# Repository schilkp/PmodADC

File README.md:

# PmodADC

### Philipp Schilk, 2020

## Description
A fully discrete 14bit, 41kHz, Successive-Approximation Audio ADC and 14bit 41kHz R2R Audio DAC 
controlled by an [iCEBreaker FPGA board](https://1bitsquared.com/collections/fpga/products/icebreaker). 

## Details

## Demos

These are a few demonstrations of the PmodADC and PmodDAC.

For each song, there are 3 files provided:  
    - The original (mono) wav file  
    - The song played back via a phone and recorded on the PmodADC  
    - The song played via the PmodDAC and recorded with a Focusrite Saffire Pro 40 Interface.  

Note that all audio files are provided at 44.1kHz to allow for easier playback:  
The PmodADC demos were played back at 44.1kHz and upsampled from 41kHz after recording.  
The PmodDAC demos were downsampled to 41kHz for playback, and recorded at 44.1kHz.   

All music by Kevin MacLeod, see Music Attribution below.

The wav files can be found [here](Doc/Demos), or via the Soundcloud links below:

| *Song* 	| *Original* 	| *PmodADC Demo* 	| *PmodDAC Demo* 	|
|:-:	|:-:	|:-:	|:-:	|
| New Hero in Town 	| [here](https://soundcloud.com/user-489490213/new-hero-in-town-reference/s-YKGpP2wkpSc) 	| [here](https://soundcloud.com/user-489490213/new-hero-in-town-pmodadc/s-A1OPIKn5Tv4) 	| [here](https://soundcloud.com/user-489490213/new-hero-in-town-pmoddac/s-smGRP41zKKE) 	|
| Protofunk 	| [here](https://soundcloud.com/user-489490213/protofunk-reference/s-mYtDzv4H0rD) 	| [here](https://soundcloud.com/user-489490213/protofunk-pmodadc/s-5CrWlwWIQJU) 	| [here](https://soundcloud.com/user-489490213/protofunk-pmoddac/s-AqIKrZKs7Aa) 	|
| Whiskey on the Mississippi 	| [here](https://soundcloud.com/user-489490213/whiskey-on-the-mississippi-reference/s-0ekaJDO2ERm) 	| [here](https://soundcloud.com/user-489490213/whiskey-on-the-mississippi-pmodadc/s-d2xfiT4uBGa) 	| [here](https://soundcloud.com/user-489490213/whiskey-on-the-mississippi-pmoddac/s-CflAaRhN0gA) 	|
| The Parting 	| [here](https://soundcloud.com/user-489490213/the-parting-reference/s-s09MCjP3SIX) 	| [here](https://soundcloud.com/user-489490213/the-parting-pmodadc/s-gcHSaS2ZzWT) 	| [here](https://soundcloud.com/user-489490213/the-parting-pmoddac/s-kLg3MuZsgWg) 	|

Alternatively, a single website with all the above audio files can be found [here](https://soundcloud.com/user-489490213/sets/pmodadc-demonstration/s-fJryQAe7XSp).

## Setup

A guide to setting up the open-source [apio](https://github.com/FPGAwars/apio) tool-chain can be found [here](Doc/ToolchainSetup.md).   

This project requires some hardware modifications to the iCEbreaker board. See [here](Doc/iCEBreakerMod.md) for details.  

The Python/Matlab scripts to play and record audio require some drivers and setup. See [here](Doc/FT2232H_Setup.md) for details.  

Two versions of the Verilog Code are provided:  
	- Setup 1, which immediately plays back the audio recorded by the PmodADC via the PmodDAC.  
	- Setup 2, which allows the PmodADC and PmodDAC to send/receive audio via USB.
	
See [here](iCEbreaker_HDL/Setup%20Description.md) for details.

## Python Utilities

The easiest way to record and play music is using the two python utilities provided [here](Scripts/Python/).

They rely on numpy, pyserial, wavio, and scipy:

```bash
> pip install -r requirements.txt
```

They have only been tested under python3.

### Record.py

Record music to a wav file using the PmodADC.

By default the audio is resampled to 44.1kHz.

Usage:

```
usage: Record.py [-h] (-s S | -n N | -i) [-r] comport outfile

positional arguments:
  comport     The COM port to which the board is connected.
  outfile     The filename under which the recorded audio should be saved.

optional arguments:
  -h, --help  show this help message and exit
  -s S        The number of seconds that should be recorded.
  -n N        The number of samples that should be recorded.
  -i          Recorded until a Keyboard Interrupt is received.
  -r          Do not re-sample audio to 44.1khz.
```

Record 10 seconds of audio from COM8 and save it to recording.wav:

```bash
python3 Record.py COM8 recording.wav -s 10
```

### Play.py

Play a wav file via the PmodDAC.

By default the wav file is resampled to 41kHz (if necessary). 

Usage:
```
usage: Play.py [-h] [-L | -R] [-r] comport wavfile

positional arguments:
  comport     The COM port to which the board is connected.
  wavfile     The filename of the audio file.

optional arguments:
  -h, --help  show this help message and exit
  -L          Play the left audio channel.
  -R          Play the right audio channel.
  -r          Do not re-sample audio to 41kHz.
```

Play the left channel of some_audio_file.wav via COM8:

```bash
python3 Play.py COM8 some_audio_file.wav -L
```

## Matlab Utilities

Matlab functions to communicate with the PmodADC/PmodDAC are also provided. 

See [Scripts/MATLAB/RecordAudioExample.m](Scripts/MATLAB/RecordAudioExample.m) and [Scripts/MATALB/PlayAudioExample.m](Scripts/MATALB/PlayAudioExample.m)

## Music Attribution

```
Protofunk by Kevin MacLeod  
Link: https://incompetech.filmmusic.io/song/4247-protofunk  
License: http://creativecommons.org/licenses/by/4.0/  

Whiskey on the Mississippi by Kevin MacLeod  
Link: https://incompetech.filmmusic.io/song/4624-whiskey-on-the-mississippi  
License: http://creativecommons.org/licenses/by/4.0/  
  
New Hero In Town by Kevin MacLeod  
Link: https://incompetech.filmmusic.io/song/5742-new-hero-in-town  
License: http://creativecommons.org/licenses/by/4.0/  

The Parting by Kevin MacLeod  
Link: https://incompetech.filmmusic.io/song/4501-the-parting  
License: http://creativecommons.org/licenses/by/4.0/  
```

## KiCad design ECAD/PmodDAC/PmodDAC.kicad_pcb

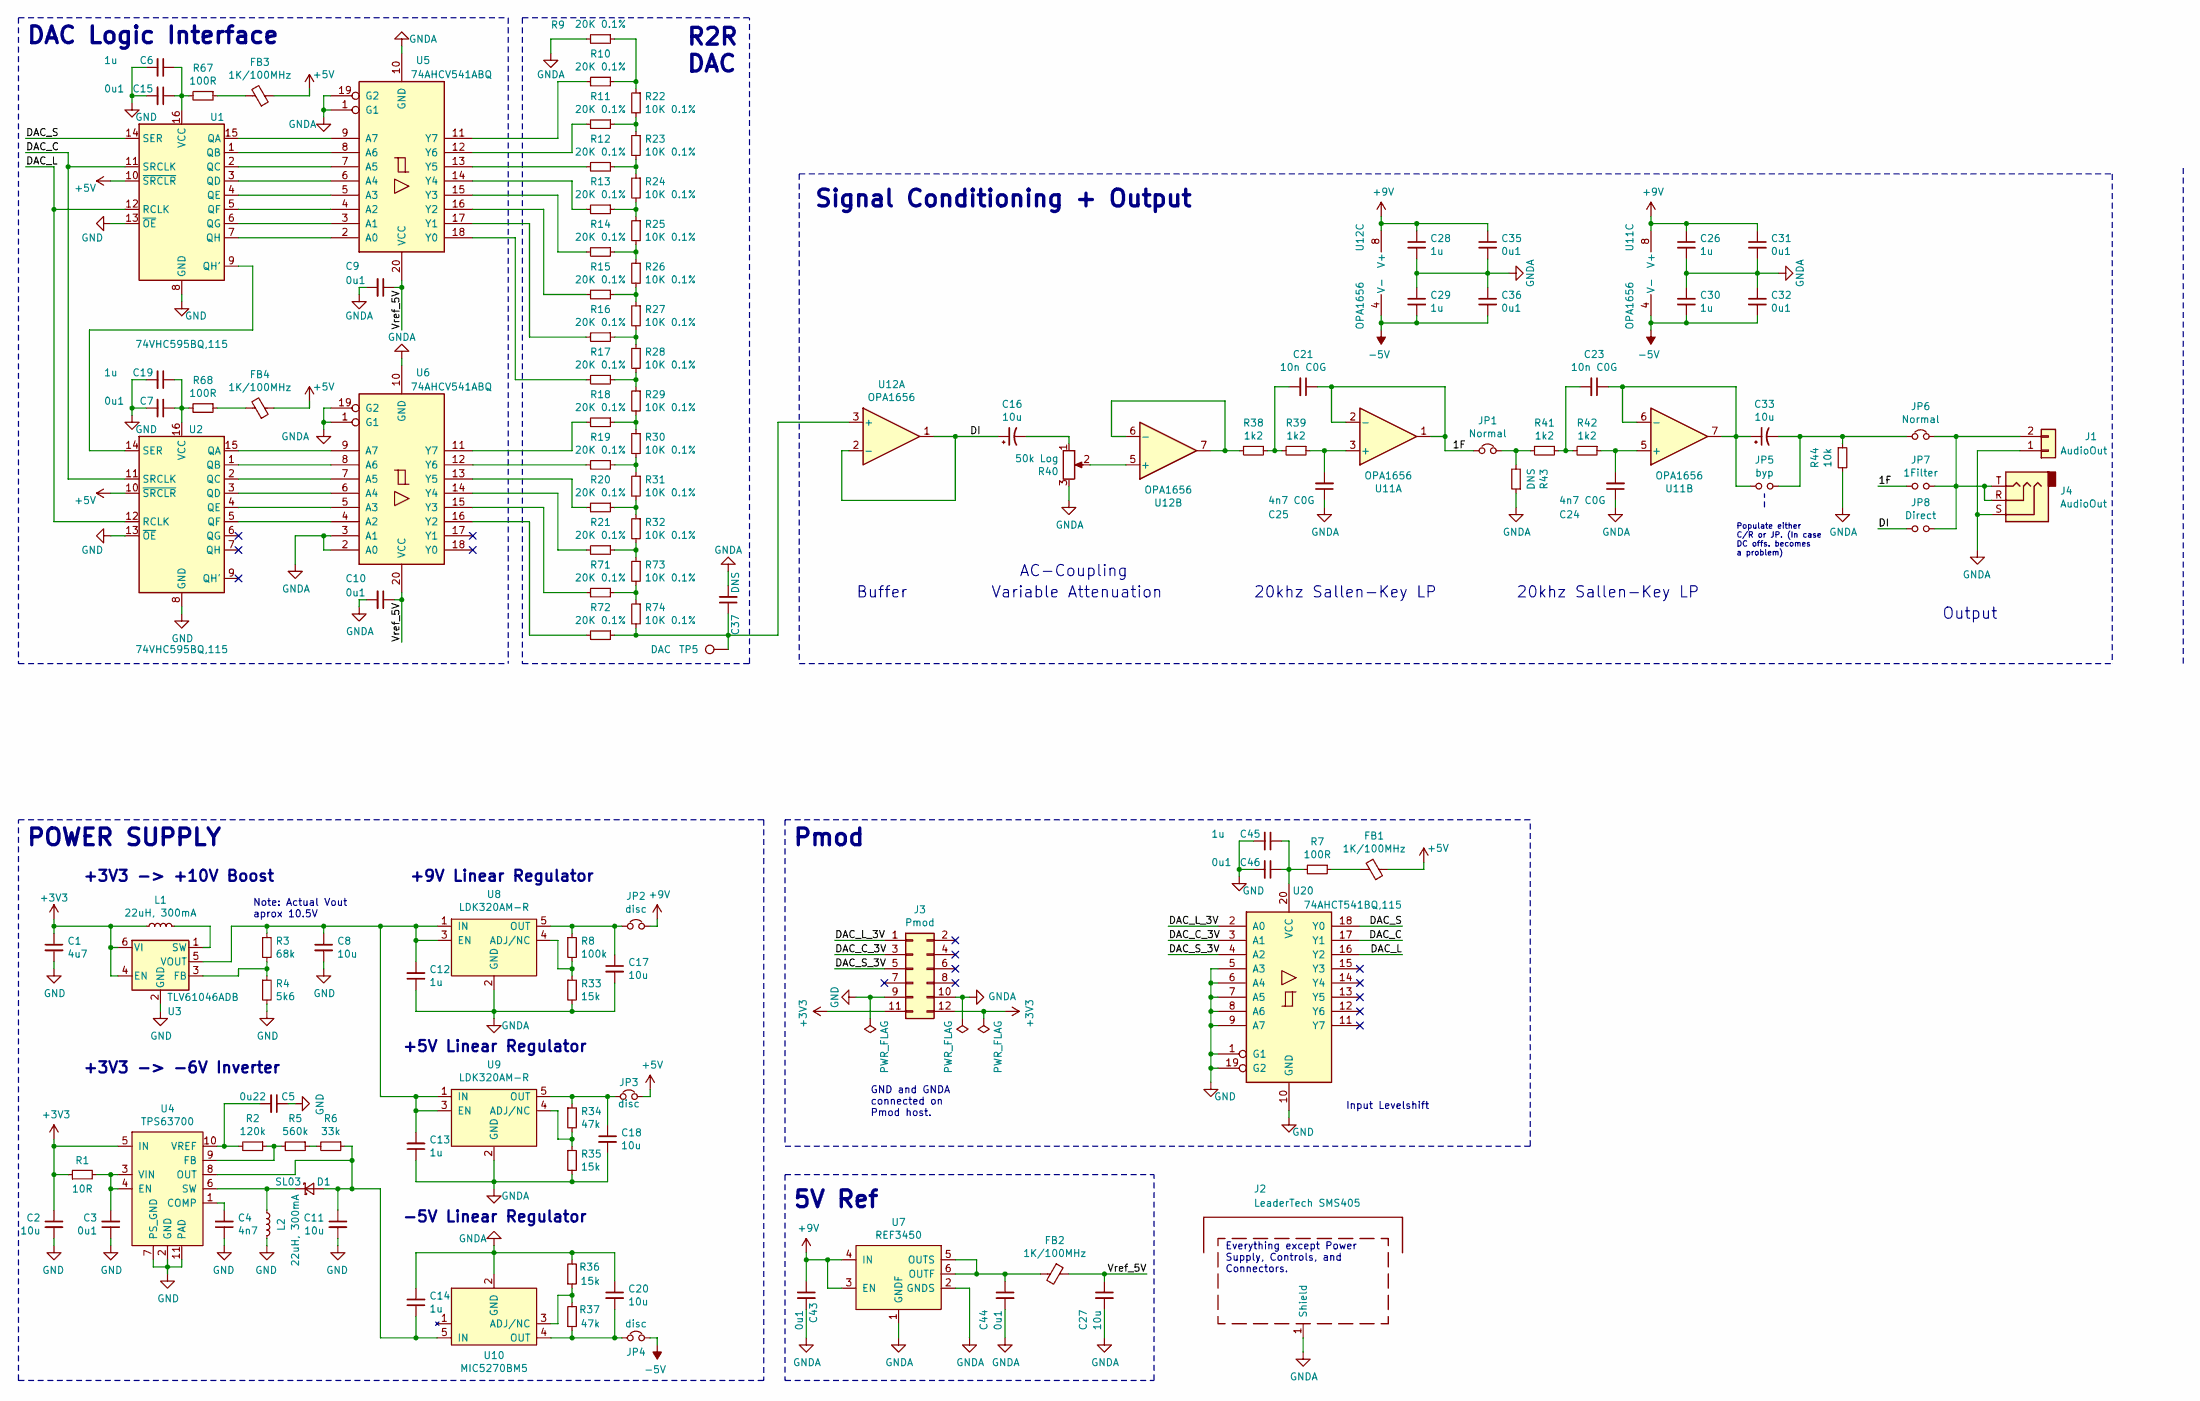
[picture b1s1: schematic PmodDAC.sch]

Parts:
C1: 4u7; C_0805_2012Metric
C2, C8, C11, C17, C18, C20, C27: 10u; C_1206_3216Metric
C3, C7, C9, C10, C15, C31, C32, C35, C36, C43, C44, C46: 0u1; C_0402_1005Metric
C4: 4n7; C_0402_1005Metric
C5: 0u22; C_0402_1005Metric
C6, C12, C13, C14, C19, C26, C28, C29, C30, C45: 1u; C_0402_1005Metric
C16, C33: 10u; CP_Radial_D4.0mm_P1.50mm
C21, C23: 10n C0G; C_0603_1608Metric
C24, C25: 4n7 C0G; C_0603_1608Metric
C37: DNS; C_0402_1005Metric
D1: SL03; D_SMF
FB1, FB2, FB3, FB4: 1K/100MHz; L_0402_1005Metric
J1: AudioOut; PinHeader_1x02_P2.54mm_Vertical
J2: LeaderTech SMS405; Leader_SMS405
J3: Pmod; PinHeader_2x06_P2.54mm_Vertical
J4: AudioOut; PJ-313D-6A
JP1, JP6: Normal; R_0402_1005Metric
JP2, JP3, JP4: disc; R_0402_1005Metric
JP5: byp; R_0402_1005Metric
JP7: 1Filter; R_0402_1005Metric
JP8: Direct; R_0402_1005Metric
L1, L2: 22uH, 300mA; L_Wuerth_MAPI-3020
R1: 10R; R_0402_1005Metric
R2: 120k; R_0402_1005Metric
R3: 68k; R_0402_1005Metric
R4: 5k6; R_0402_1005Metric
R5: 560k; R_0402_1005Metric
R6: 33k; R_0402_1005Metric
R7, R67, R68: 100R; R_0402_1005Metric
R8: 100k; R_0402_1005Metric
R9, R10, R11, R12, R13, R14, R15, R16, R17, R18, R19, R20, R21, R71, R72: 20K 0.1%; R_0402_1005Metric
R22, R23, R24, R25, R26, R27, R28, R29, R30, R31, R32, R73, R74: 10K 0.1%; R_0402_1005Metric
R33, R35, R36: 15k; R_0402_1005Metric
R34, R37: 47k; R_0402_1005Metric
R38, R39, R41, R42: 1k2; R_0402_1005Metric
R40: 50k Log; Potentiometer_Alps_RK09L_Single_Vertical
R43: DNS; R_0402_1005Metric
R44: 10k; R_0402_1005Metric
TP5: DAC; TestPoint_Pad_D1.0mm
U1, U2: 74VHC595BQ,115; SOT763-1_DHVQFN16
U3: TLV61046ADB; SOT-23-6
U4: TPS63700; VSON-10-1EP_3x3mm_P0.5mm_EP1.65x2.4mm_ThermalVias
U5, U6: 74AHCV541ABQ; SOT764-1_DHVQFN20
U7: REF3450; SOT-23-6
U8, U9: LDK320AM-R; SOT-23-5
U10: MIC5270BM5; SOT-23-5
U11, U12: OPA1656; SOIC-8_3.9x4.9mm_P1.27mm
U20: 74AHCT541BQ,115; SOT764-1_DHVQFN20

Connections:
+3V3: C1.1, C2.1, J3.11, J3.12, L1.1, R1.1, U3.4 (EN), U3.6 (VI), U4.5 (IN)
+5V: FB1.1, FB3.1, FB4.1, JP3.2, U1.10 (~SRCLR), U2.10 (~SRCLR)
+9V: C26.1, C28.1, C31.1, C35.1, C43.1, JP2.2, U7.3 (EN), U7.4 (IN), U11.8 (V+), U12.8 (V+)
-5V: C29.2, C30.2, C32.2, C36.2, JP4.2, U11.4 (V-), U12.4 (V-)
/1F: C21.1, JP1.1, JP7.1, U11.1, U11.2 (-)
/DAC_C: U1.11 (SRCLK), U2.11 (SRCLK), U20.17 (Y1)
/DAC_C_3V: J3.3, U20.3 (A1)
/DAC_L: U1.12 (RCLK), U2.12 (RCLK), U20.16 (Y2)
/DAC_L_3V: J3.1, U20.2 (A0)
/DAC_S: U1.14 (SER), U20.18 (Y0)
/DAC_S_3V: J3.5, U20.4 (A2)
/DI: C16.1, JP8.1, U12.1, U12.2 (-)
/Vref_5V: C9.1, C10.1, C27.1, FB2.1, U5.20 (VCC), U6.20 (VCC)
GND: C1.2, C2.2, C3.1, C4.1, C5.1, C6.2, C7.2, C8.2, C11.2, C15.2, C19.2, C45.2, C46.2, J3.9, L2.2, R4.2, U1.8 (GND), U1.13 (~OE), U2.8 (GND), U2.13 (~OE), U3.2 (GND), U4.2 (GND), U4.7 (PS_GND), U4.11 (PAD), U20.1 (G1), U20.5 (A3), U20.6 (A4), U20.7 (A5), U20.8 (A6), U20.9 (A7), U20.10 (GND), U20.19 (G2)
GNDA: C9.2, C10.2, C12.1, C13.1, C14.2, C17.2, C18.2, C20.1, C24.1, C25.1, C26.2, C27.2, C28.2, C29.1, C30.1, C31.2, C32.1, C35.2, C36.1, C37.2, C43.2, C44.2, J1.1, J2.1, J3.10, J4.S, R9.2, R33.2, R35.2, R36.2, R40.3, R43.1, R44.2, U5.1 (G1), U5.10 (GND), U5.19 (G2), U6.1 (G1), U6.2 (A0), U6.3 (A1), U6.10 (GND), U6.19 (G2), U7.1 (GNDF), U7.2 (GNDS), U8.2 (GND), U9.2 (GND), U10.2 (GND)
unnamed: C3.2, R1.2, U4.3 (VIN), U4.4 (EN)
unnamed: C4.2, U4.1 (COMP)
unnamed: C5.2, R2.2, U4.10 (VREF)
unnamed: C11.1, C14.1, D1.2 (A), R6.1, U4.8 (OUT), U10.5 (IN)
unnamed: C8.1, C12.2, C13.2, R3.1, U3.5 (VOUT), U8.1 (IN), U8.3 (EN), U9.1 (IN), U9.3 (EN)
unnamed: C6.1, C15.1, R67.2, U1.16 (VCC)
unnamed: C16.2, R40.1
unnamed: C17.1, JP2.1, R8.1, U8.5 (OUT)
unnamed: C18.1, JP3.1, R34.1, U9.5 (OUT)
unnamed: C7.1, C19.1, R68.2, U2.16 (VCC)
unnamed: C20.2, JP4.1, R37.1, U10.4 (OUT)
unnamed: C21.2, R38.1, R39.2
unnamed: C23.1, C33.1, JP5.1, U11.6 (-), U11.7
unnamed: C23.2, R41.1, R42.2
unnamed: C24.2, R42.1, U11.5 (+)
unnamed: C25.2, R39.1, U11.3 (+)
unnamed: C33.2, JP5.2, JP6.1, R44.1
unnamed: C37.1, R72.1, R74.2, TP5.1, U12.3 (+)
unnamed: C44.1, FB2.2, U7.5 (OUTS), U7.6 (OUTF)
unnamed: C45.1, C46.1, R7.2, U20.20 (VCC)
unnamed: D1.1 (K), L2.1, U4.6 (SW)
unnamed: FB1.2, R7.1
unnamed: FB3.2, R67.1
unnamed: FB4.2, R68.1
unnamed: J1.2, J4.R, J4.T, JP6.2, JP7.2, JP8.2
unnamed: JP1.2, R41.2, R43.2
unnamed: L1.2, U3.1 (SW)
unnamed: R2.1, R5.2, U4.9 (FB)
unnamed: R3.2, R4.1, U3.3 (FB)
unnamed: R5.1, R6.2
unnamed: R9.1, R10.1, R22.1
unnamed: R10.2, U5.11 (Y7)
unnamed: R11.1, R22.2, R23.1
unnamed: R11.2, U5.12 (Y6)
unnamed: R12.1, R23.2, R24.1
unnamed: R12.2, U5.13 (Y5)
unnamed: R13.1, R24.2, R25.1
unnamed: R13.2, U5.14 (Y4)
unnamed: R14.1, R25.2, R26.1
unnamed: R14.2, U5.15 (Y3)
unnamed: R15.1, R26.2, R27.1
unnamed: R15.2, U5.16 (Y2)
unnamed: R16.1, R27.2, R28.1
unnamed: R16.2, U5.17 (Y1)
unnamed: R17.1, R28.2, R29.1
unnamed: R17.2, U5.18 (Y0)
unnamed: R18.1, R29.2, R30.1
unnamed: R18.2, U6.11 (Y7)
unnamed: R19.1, R30.2, R31.1
unnamed: R19.2, U6.12 (Y6)
unnamed: R20.1, R31.2, R32.1
unnamed: R20.2, U6.13 (Y5)
unnamed: R21.1, R32.2, R73.1
unnamed: R21.2, U6.14 (Y4)
unnamed: R8.2, R33.1, U8.4 (ADJ/NC)
unnamed: R34.2, R35.1, U9.4 (ADJ/NC)
unnamed: R36.1, R37.2, U10.3 (ADJ/NC)
unnamed: R38.2, U12.6 (-), U12.7
unnamed: R40.2, U12.5 (+)
unnamed: R71.1, R73.2, R74.1
unnamed: R71.2, U6.15 (Y3)
unnamed: R72.2, U6.16 (Y2)
unnamed: U1.1 (QB), U5.8 (A6)
unnamed: U1.2 (QC), U5.7 (A5)
unnamed: U1.3 (QD), U5.6 (A4)
unnamed: U1.4 (QE), U5.5 (A3)
unnamed: U1.5 (QF), U5.4 (A2)
unnamed: U1.6 (QG), U5.3 (A1)
unnamed: U1.7 (QH), U5.2 (A0)
unnamed: U1.9 (QH'), U2.14 (SER)
unnamed: U1.15 (QA), U5.9 (A7)
unnamed: U2.1 (QB), U6.8 (A6)
unnamed: U2.2 (QC), U6.7 (A5)
unnamed: U2.3 (QD), U6.6 (A4)
unnamed: U2.4 (QE), U6.5 (A3)
unnamed: U2.5 (QF), U6.4 (A2)
unnamed: U2.15 (QA), U6.9 (A7)

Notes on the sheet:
+5V Linear Regulator
R2R DAC
POWER SUPPLY
DAC Logic Interface
Pmod
5V Ref
+9V Linear Regulator
-5V Linear Regulator
+3V3 -> +10V Boost
+3V3 -> -6V Inverter
Note: Actual Vout aprox 10.5V
20khz Sallen-Key LP
Buffer
Signal Conditioning + Output
Input Levelshift
Everything except Power Supply, Controls, and Connectors.
GND and GNDA connected on Pmod host.
Variable Attenuation
AC-Coupling
Output
Populate either C/R or JP. (In case DC offs. becomes a problem)

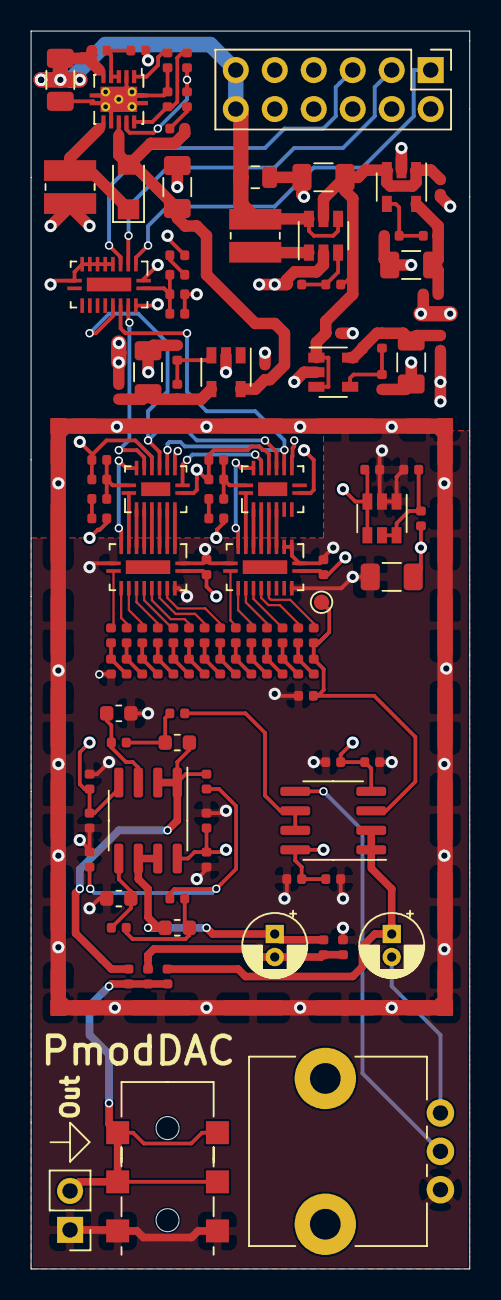
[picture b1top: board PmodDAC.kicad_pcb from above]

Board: 4 copper layers, 28.6 x 80.6 mm, 122 parts (0 on the bottom side), 92 nets.

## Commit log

2020-09-23 Rename
2020-10-11 PCB v0.0 Done.
2020-10-11 First draft Schematic
2020-10-11 Reworked Power Scheme
2020-10-12 Generated Production Files
2020-10-12 Quickfix PCB v0.1
2020-10-25 Shiftout interface module working
2020-10-25 Basic Testbench setup
2020-10-25 First Succesfull ADC and DAC hardware test
2020-10-25 Project Setup
2020-10-25 First draft ADC HW working
2020-10-25 First draft of A-to-D working in Simulationwip
    First draft of A-to-D working in Simulation
2020-10-25 Added TODOs
2020-10-30 Finished Schematic Design
2020-10-31 Added Footprints, fixedup Schematic, Cleanup
2020-10-31 First Draft Layout PmodADC done
2020-10-31 Re-Simulated audio output
2020-10-31 First draft DAC PCB done
2020-11-01 Added html ignore for language stats
2020-11-01 Generated ADC Produciton Files
2020-11-01 Added DAC Production Files
2020-11-02 Fixed HTML ignore.
2020-11-02 Added S&H Trace Image
2020-11-03 Updated changelog to v0.2
2020-11-04 Added Sample Recording
2020-11-14 Changed Pinout to v0.1 in Code
2020-11-19 Documentation work + slight restructure.
2020-11-19 Fixed image link
2020-11-20 Cleaned up code and added comments
2020-11-20 Removed Reset (Pin used by FTDI FIFO interface)
2020-11-20 FIFO TX first working :)
2020-11-20 Decoupled RX and TX in fifo interface
2020-11-20 Cleanup
2020-11-20 First draft Audio Interface working, bottleneckt?
2020-11-20 Python Test Scripts
2020-11-20 Fixed Changed Samplerate from debugging
2020-11-20 Added Documentation
2020-11-21 Documented Jumpers
2020-11-21 Updated FIFO test to reflect ADC data rate.
2020-11-21 Fixed broken image link
2020-11-22 First Signs of Life
2020-11-25 Reduced on-time for error LEDs
2020-11-25 Recording working via cmdl->file, not in python
2020-11-25 Python Recording Working!
    Combination of:
    Preallocating Storage
    Reading more than 1 byte on each call of serial.read
    will investigate which one actually made a difference
2020-11-25 Confirmed pyserial's read() overhead as problem.
    Moving back to dynamic memory allocation, as it is more
    flexible.
2020-11-25 Refactored Code
2020-11-25 Documented Code
2020-11-25 First draft Matlab record working
2020-11-25 Added Receive Simulation to Testbench
2020-11-26 Updated Matlab
2020-11-26 Changed RX LED to shine on success
2020-11-26 Updated FIFO test to also RX at correct speeds
2020-11-27 Always update DAC at constant rate
2020-11-27 Organisational Cleanup
2020-11-27 Code Cleanup
2020-11-27 Single DAC set working
2020-11-27 fixed broken links
2020-11-27 Added Information on Driver Setup
2020-11-27 Changed RX led back to error indicator
2020-11-27 Computer playback mostly working
    Still drops a sample or two every second
2020-11-27 Cleaned-up/Consolidated dac_play/dac_set
2020-11-27 Wrapped up MATLAB scripts
2020-11-27 Quick ADC Noise Test
2020-11-28 Changed record time in Matlab example to be something more sensible.
2020-11-29 Play working but bootleknecked. Python clean/refac
2020-11-29 Threaded Packaging during play working.
2020-11-29 Added Bias Adj. script, adjusted bias
2020-11-29 Fixed typo
2020-11-29 Ignore all .wav in Scripts folder
2020-11-29 Reworked/Fixed ADC Noise test
2020-12-07 Fixed small errors in Play.py
2020-12-08 removed recording.
2020-12-08 Added Reference Tracks
2020-12-09 Added Images
2020-12-09 Added automatic resampling to MATLAB examples
2020-12-09 Added PmodADC refernce tracks
2020-12-09 Fixed Attribution Formating
2020-12-10 Added Resampling to Python Scripts
2020-12-10 Documentation Work
2020-12-10 Updated help output of python scripts
2020-12-10 Small README typos
2020-12-10 Renamed Folder
2020-12-10 Fixed Closing Port
2020-12-10 Characteristation Outlines
2020-12-11 Lab WIP
2020-12-13 First Processing Draft
2020-12-13 Added PDF reports
2020-12-13 Small fix
2020-12-14 Added PmodDAC Demos
2020-12-14 Fixed small typo
2020-12-14 Fixed Broken link
2020-12-14 Fixed Links
2020-12-14 Improved Image
2020-12-16 Added Presentation
2021-05-24 Ignore LTSpice in language stats
